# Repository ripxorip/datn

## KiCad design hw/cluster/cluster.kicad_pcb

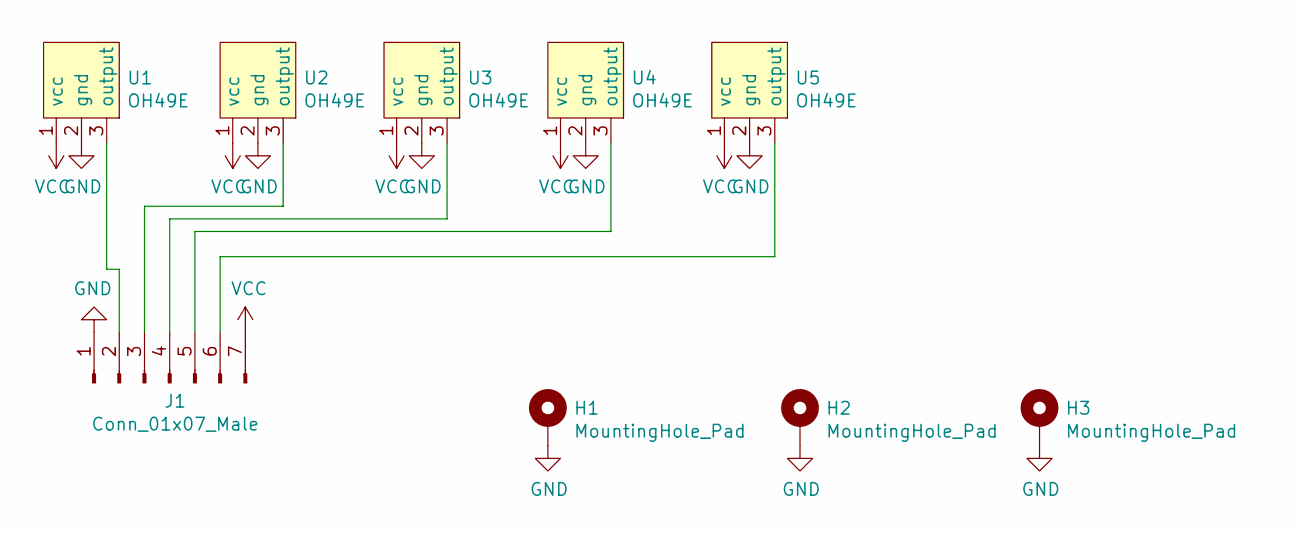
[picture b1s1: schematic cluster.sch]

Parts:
H1, H2, H3: MountingHole_Pad; MountingHole_2.2mm_M2_Pad_Via
J1: Conn_01x07_Male; cluster_connector_pcb_small
U1, U2, U3, U4, U5: OH49E

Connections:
GND: H1.1, H2.1, H3.1, J1.1, U1.2 (gnd), U2.2 (gnd), U3.2 (gnd), U4.2 (gnd), U5.2 (gnd)
unnamed: J1.2, U1.3 (output)
unnamed: J1.3, U2.3 (output)
unnamed: J1.4, U3.3 (output)
unnamed: J1.5, U4.3 (output)
unnamed: J1.6, U5.3 (output)
VCC: J1.7, U1.1 (vcc), U2.1 (vcc), U3.1 (vcc), U4.1 (vcc), U5.1 (vcc)

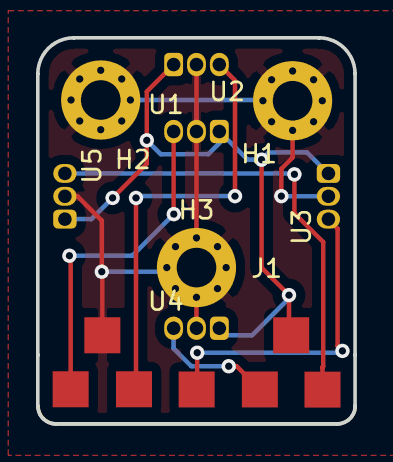
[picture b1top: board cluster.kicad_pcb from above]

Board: 2 copper layers, 17.6 x 21.5 mm, 9 parts (0 on the bottom side), 7 nets.

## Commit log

2021-12-23 First working proof of concept
2021-12-26 Adds initial version of the cluster PCB
2021-12-30 Adds pi pico-sdk
2021-12-30 ADC and multiplexer verified with statisfying result, next up initial cluster DSP and i2c
2021-12-31 Adds some cluster love, next up i2c
2022-01-01 Working i2c
